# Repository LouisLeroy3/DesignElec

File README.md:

#
# Collaborateur

Ce travail a été réalisé avec l'aide de Valentin Boutouria, car Valentin ne pouvait pas faire fonctionner le logiciel (malgré la bonne volonté des professeurs).

# Design
TP de design sur la partie électronique du Key Finder

# Objectif du projet

Crée la carte du KeyFinder sur un logiciel de design électronique Kicad.

# Objectif atteint

Carte et ajout d'un bouton et d'un buzzer.

# Limitations

Nous n'avons pas reussi a faire l'entièreté des focntions 

# Sources

Ce projet est inspiré des templates sur Kicad

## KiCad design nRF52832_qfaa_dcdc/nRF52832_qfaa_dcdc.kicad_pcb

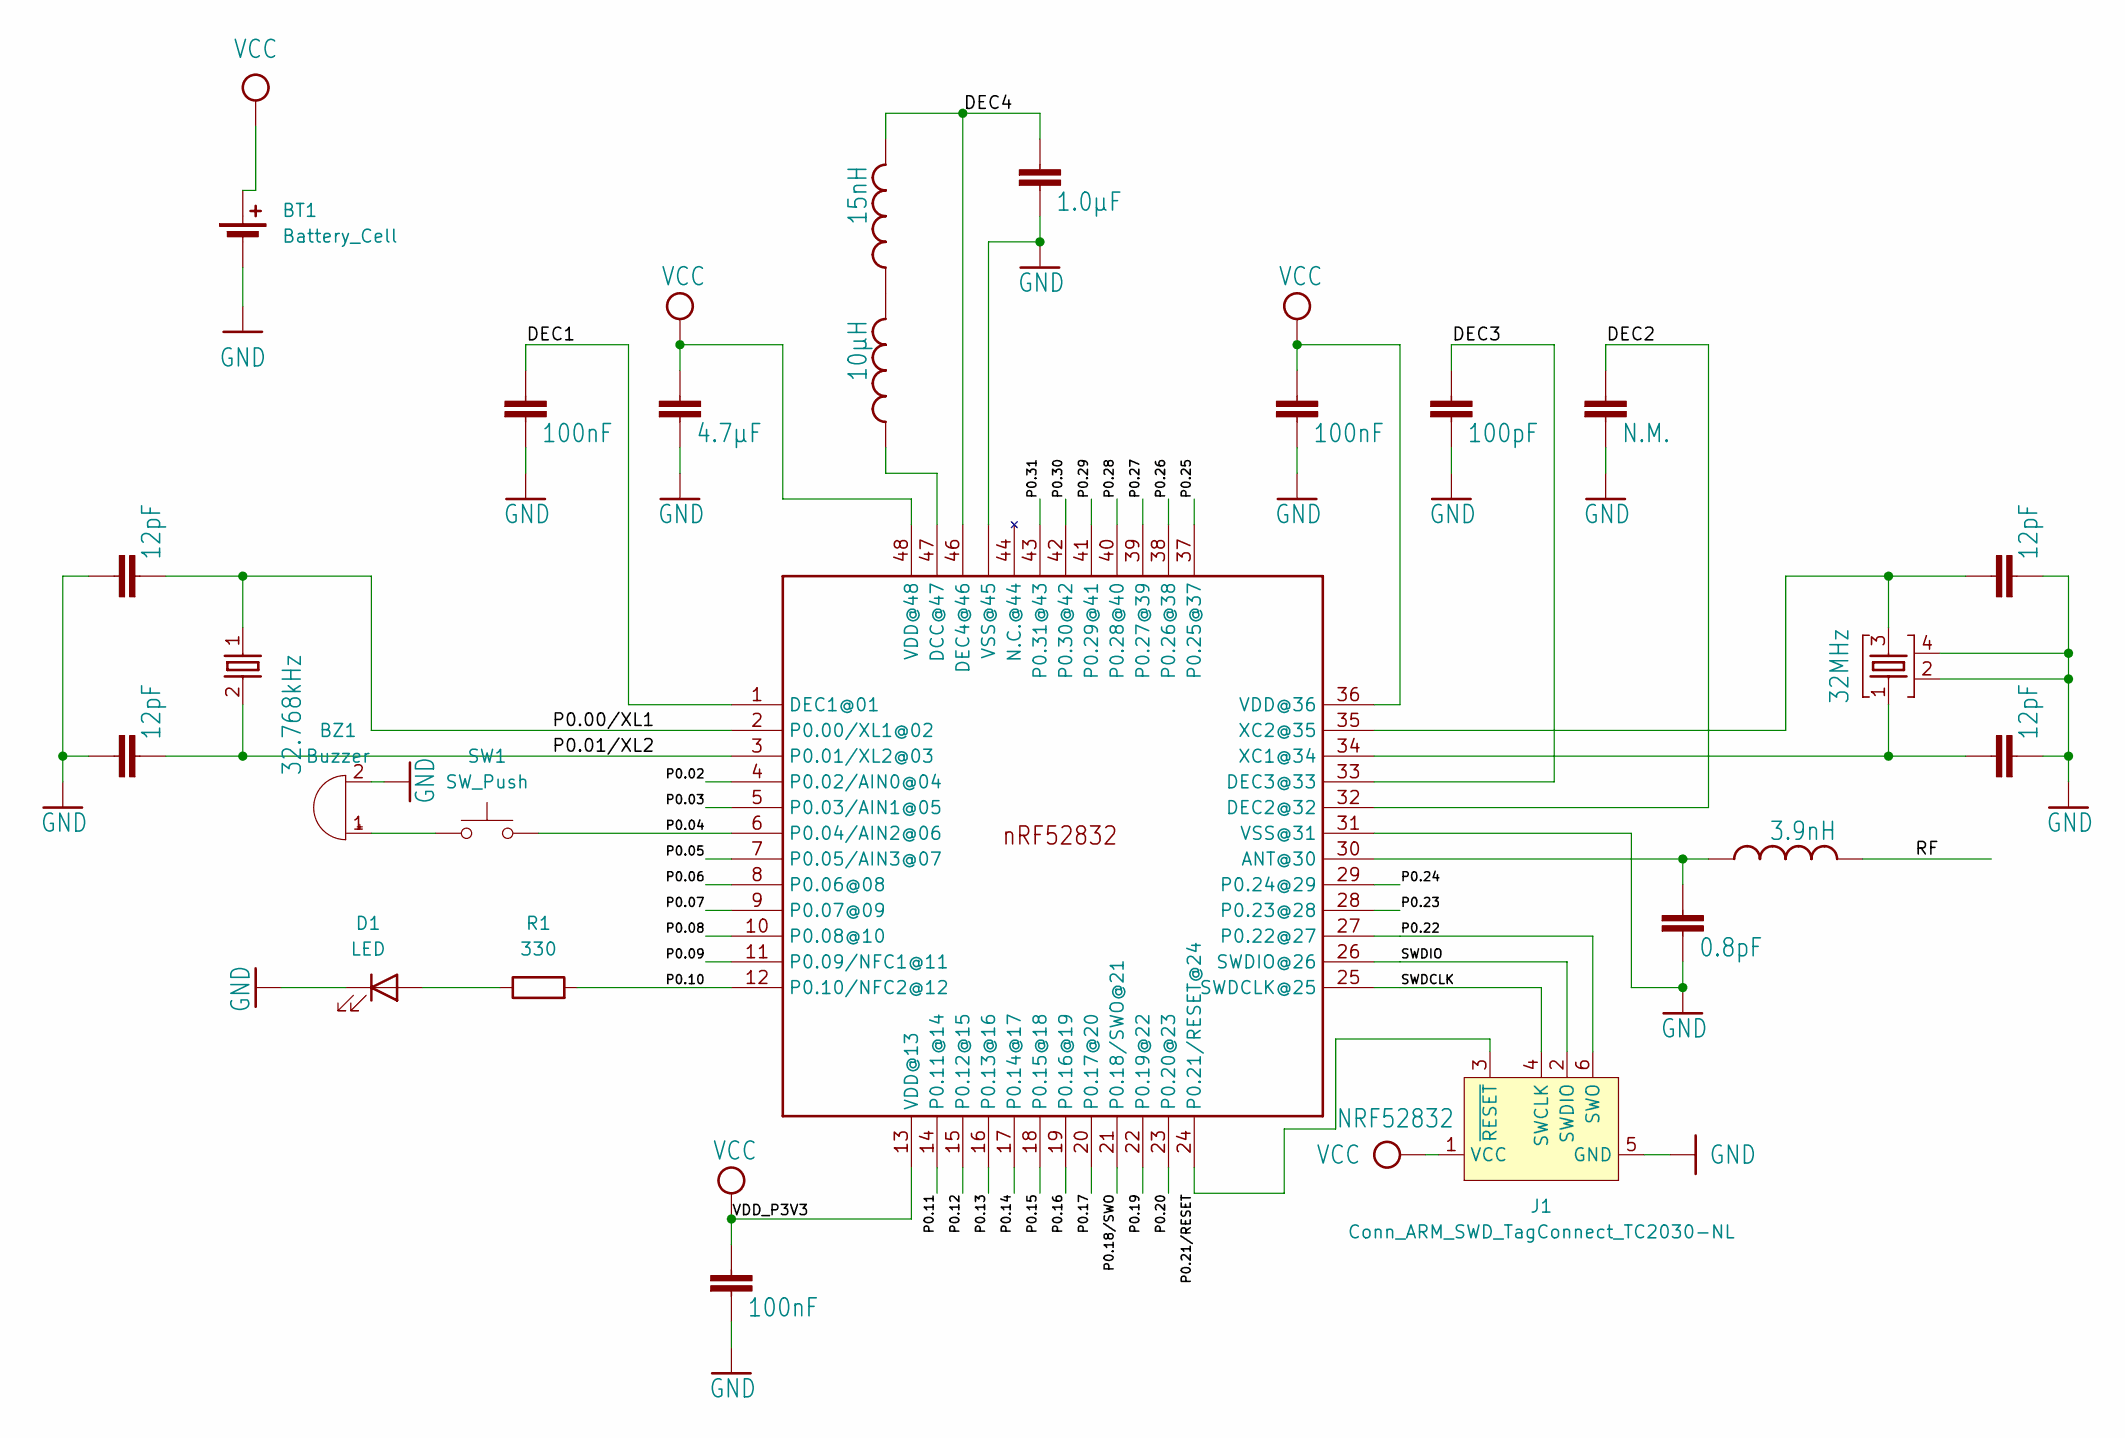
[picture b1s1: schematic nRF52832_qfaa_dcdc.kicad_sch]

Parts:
BT1: Battery_Cell; Buzzer_Mallory_AST1240MLQ
BZ1: Buzzer; Buzzer_Mallory_AST1240MLQ
C1, C2, C11, C12: 12pF; RESC0402_N
C3: 0.8pF; RESC0402_N
C4, C5, C8: 100nF; RESC0402_N
C6: N.M.; RESC0402_N
C7: 100pF; RESC0402_N
C9: 4.7µF; RESC0603_N
C10: 1.0µF; RESC0603_N
D1: LED; D_0805_2012Metric
J1: Conn_ARM_SWD_TagConnect_TC2030-NL; Tag-Connect_TC2030-IDC-NL_2x03_P1.27mm_Vertical
L1: 3.9nH; RESC0402_N
L2: 10µH; RESC0603_N
L3: 15nH; RESC0402_N
R1: 330; R_0805_2012Metric
SW1: SW_Push; SW_CW_GPTS203211B
U1: NRF52832; QFN40P600X600X90-48_N
X1: 32MHz; BT-XTAL_2016_N
X2: 32.768kHz; XTAL_3215_N

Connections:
/DEC1: C4.1, U1.1 (DEC1@01)
/DEC2: C6.1, U1.32 (DEC2@32)
/DEC3: C7.1, U1.33 (DEC3@33)
/DEC4: C10.1, L3.2, U1.46 (DEC4@46)
/P0.00/XL1: C11.2, U1.2 (P0.00/XL1@02), X2.1
/P0.01/XL2: C12.2, U1.3 (P0.01/XL2@03), X2.2
/P0.02: U1.4 (P0.02/AIN0@04)
/P0.03: U1.5 (P0.03/AIN1@05)
/P0.04: SW1.2, U1.6 (P0.04/AIN2@06)
/P0.05: U1.7 (P0.05/AIN3@07)
/P0.06: U1.8 (P0.06@08)
/P0.07: U1.9 (P0.07@09)
/P0.08: U1.10 (P0.08@10)
/P0.09: U1.11 (P0.09/NFC1@11)
/P0.10: R1.2, U1.12 (P0.10/NFC2@12)
/P0.11: U1.14 (P0.11@14)
/P0.12: U1.15 (P0.12@15)
/P0.13: U1.16 (P0.13@16)
/P0.14: U1.17 (P0.14@17)
/P0.15: U1.18 (P0.15@18)
/P0.16: U1.19 (P0.16@19)
/P0.17: U1.20 (P0.17@20)
/P0.18/SWO: U1.21 (P0.18/SWO@21)
/P0.19: U1.22 (P0.19@22)
/P0.20: U1.23 (P0.20@23)
/P0.21/RESET: J1.3 (~RESET), U1.24 (P0.21/RESET@24)
/P0.22: J1.6 (SWO), U1.27 (P0.22@27)
/P0.23: U1.28 (P0.23@28)
/P0.24: U1.29 (P0.24@29)
/P0.25: U1.37 (P0.25@37)
/P0.26: U1.38 (P0.26@38)
/P0.27: U1.39 (P0.27@39)
/P0.28: U1.40 (P0.28@40)
/P0.29: U1.41 (P0.29@41)
/P0.30: U1.42 (P0.30@42)
/P0.31: U1.43 (P0.31@43)
/RF: L1.2
/SWDCLK: J1.4 (SWCLK), U1.25 (SWDCLK@25)
/SWDIO: J1.2 (SWDIO), U1.26 (SWDIO@26)
GND: BT1.2 (-), BZ1.2 (+), C1.2, C2.2, C3.2, C4.2, C5.2, C6.2, C7.2, C8.2, C9.2, C10.2, C11.1, C12.1, D1.1 (K), J1.5 (GND), U1.31 (VSS@31), U1.45 (VSS@45), U1.PAD (VSS@45), U1.PAD@VIA01 (VSS@45), U1.PAD@VIA02 (VSS@45), U1.PAD@VIA03 (VSS@45), U1.PAD@VIA04 (VSS@45), U1.PAD@VIA05 (VSS@45), U1.PAD@VIA06 (VSS@45), U1.PAD@VIA07 (VSS@45), U1.PAD@VIA08 (VSS@45), U1.PAD@VIA09 (VSS@45), U1.PAD@VIA10 (VSS@45), U1.PAD@VIA11 (VSS@45), U1.PAD@VIA12 (VSS@45), U1.PAD@VIA13 (VSS@45), U1.PAD@VIA14 (VSS@45), U1.PAD@VIA15 (VSS@45), U1.PAD@VIA16 (VSS@45), X1.2, X1.4
unnamed: BZ1.1 (-), SW1.1
unnamed: D1.2 (A), R1.1
unnamed: L2.2, L3.1
unnamed: C3.1, L1.1, U1.30 (ANT@30)
unnamed: L2.1, U1.47 (DCC@47)
unnamed: C1.1, U1.34 (XC1@34), X1.1
unnamed: C2.1, U1.35 (XC2@35), X1.3
VCC: BT1.1 (+), C5.1, C8.1, C9.1, J1.1 (VCC), U1.13 (VDD@13), U1.36 (VDD@36), U1.48 (VDD@48)

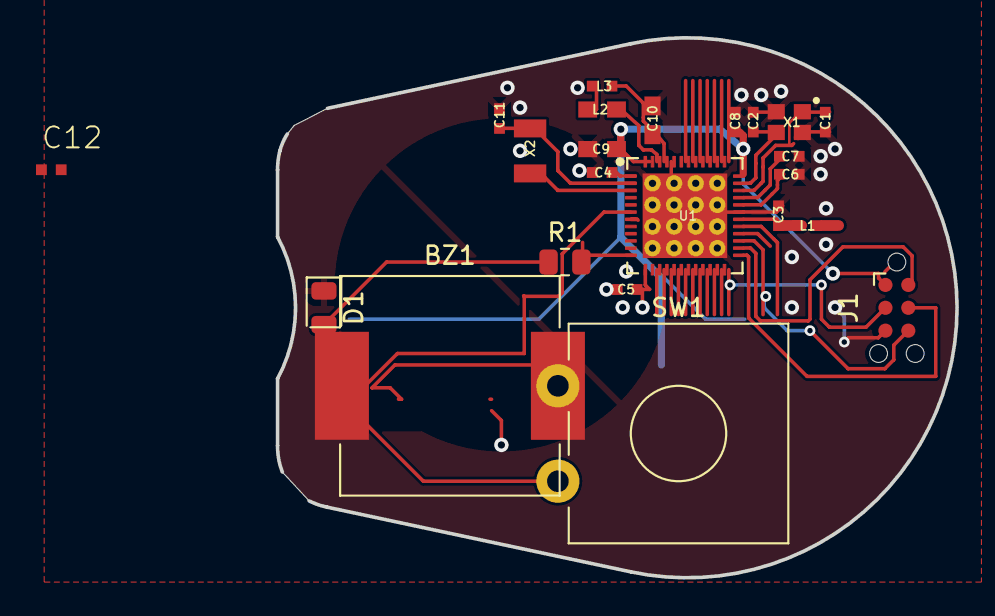
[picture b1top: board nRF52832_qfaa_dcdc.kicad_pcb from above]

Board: 2 copper layers, 37.8 x 30.0 mm, 24 parts (1 on the bottom side), 21 nets.

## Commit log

2023-11-20 First commit
    DEbut avec led et resistance
2023-11-20 add read me
2023-11-20 Save
2023-11-20 Ajout bouton et buzzer
2023-11-20 Mapping pour bouton et buzzer
2023-11-20 Finale
2023-11-27 Avancée du Read Me
2023-12-04 commit changement elec
